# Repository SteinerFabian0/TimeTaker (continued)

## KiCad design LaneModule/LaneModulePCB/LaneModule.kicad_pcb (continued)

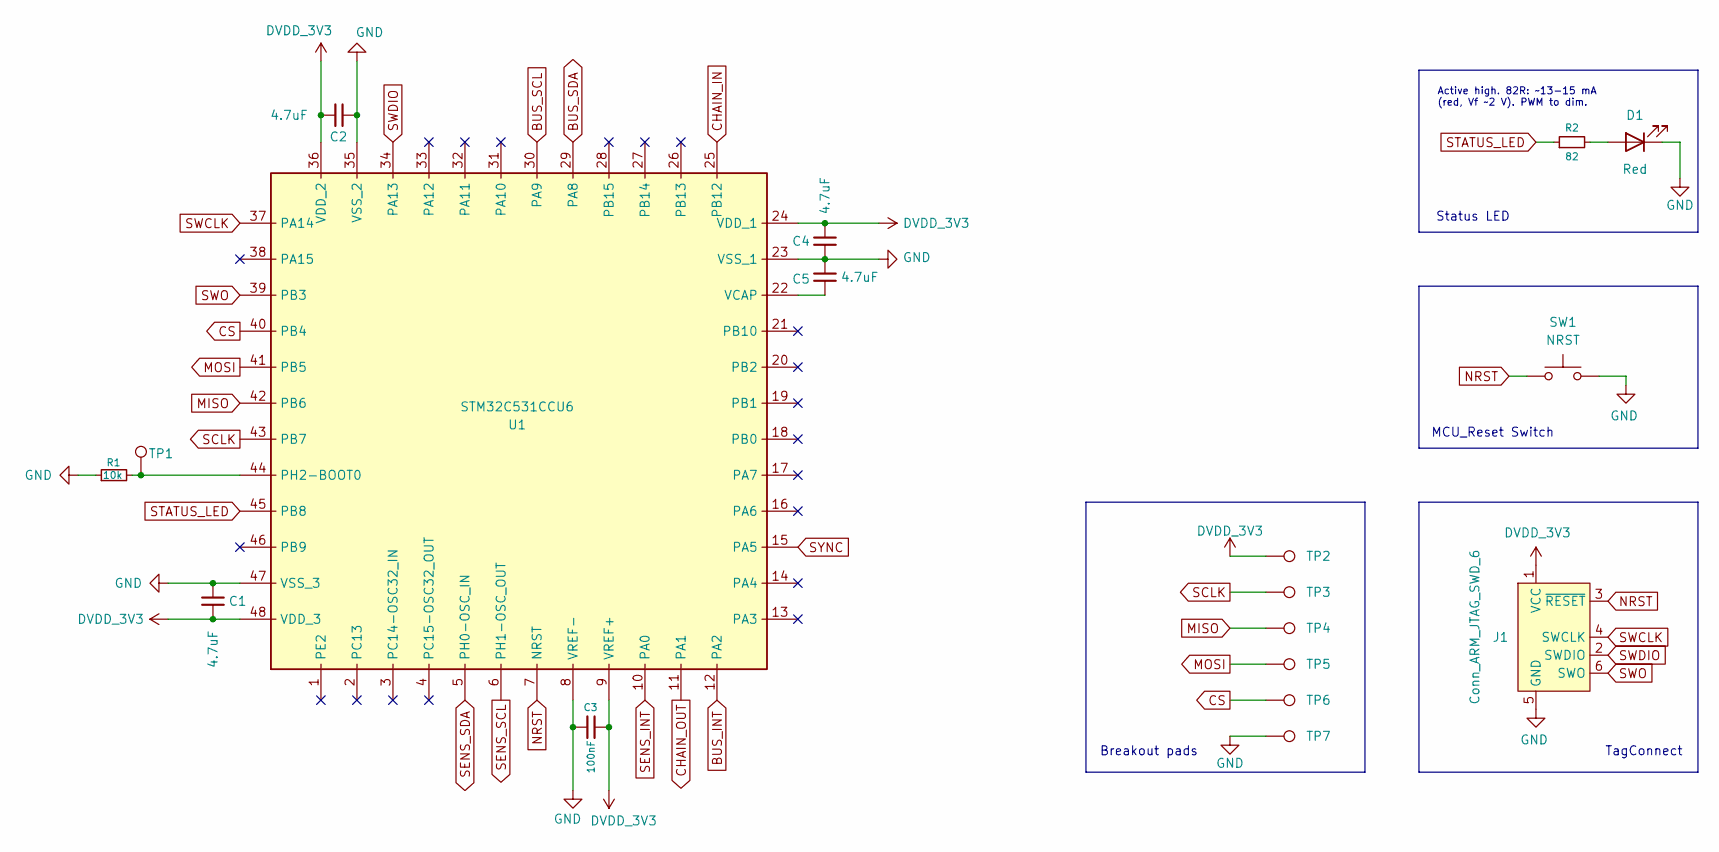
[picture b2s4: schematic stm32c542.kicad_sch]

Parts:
C1, C2, C4, C5: 4.7uF; C_0402_1005Metric; MPN CL05A475MP5NRNC; LCSC C23733
C3: 100nF; C_0402_1005Metric; MPN CL05B104KO5NNNC; LCSC C1525
D1: Red; LED_D5.0mm
J1: Conn_ARM_JTAG_SWD_6; Tag-Connect_TC2030-IDC-NL_2x03_P1.27mm_Vertical
R1: 10k; R_0603_1608Metric
R2: 82; R_0603_1608Metric
SW1: NRST; SW_SPST_TS-1088-xR025; MPN TS-1088-AR02016; LCSC C720477
TP1: TestPoint; Testpoint_1.2mm
TP2, TP3, TP4, TP5, TP6, TP7: TestPoint; TestPoint_Pad_1.5x1.5mm
U1: STM32C531CCU6; QFN50P700X700X60-49N-D; Manufacturer_Part_Number STM32C531CCU6

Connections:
BUS_INT: U1.12 (PA2); also elsewhere on the board
BUS_SCL: U1.30 (PA9); also elsewhere on the board
BUS_SDA: U1.29 (PA8); also elsewhere on the board
CHAIN_IN: U1.25 (PB12); also elsewhere on the board
CHAIN_OUT: U1.11 (PA1); also elsewhere on the board
CS: TP6.1 (1_1), U1.40 (PB4)
DVDD_3V3: C1.2, C2.2, C3.2, C4.1, J1.1 (VCC), TP2.1 (1_1), U1.9 (VREF+), U1.24 (VDD_1), U1.36 (VDD_2), U1.48 (VDD_3); also elsewhere on the board
GND: C1.1, C2.1, C3.1, C4.2, C5.1, D1.1 (K), J1.5 (GND), R1.1, SW1.2, TP7.1 (1_1), U1.8 (VREF-), U1.23 (VSS_1), U1.35 (VSS_2), U1.47 (VSS_3), U1.49 (VSS_4); also elsewhere on the board
MISO: TP4.1 (1_1), U1.42 (PB6)
MOSI: TP5.1 (1_1), U1.41 (PB5)
NRST: J1.3 (~RESET), SW1.1, U1.7 (NRST)
unnamed: D1.2 (A), R2.2
unnamed: R1.2, TP1.1 (1_1), U1.44 (PH2-BOOT0)
unnamed: C5.2, U1.22 (VCAP)
SCLK: TP3.1 (1_1), U1.43 (PB7)
SENS_INT: U1.10 (PA0); also elsewhere on the board
SENS_SCL: U1.6 (PH1-OSC_OUT); also elsewhere on the board
SENS_SDA: U1.5 (PH0-OSC_IN); also elsewhere on the board
STATUS_LED: R2.1, U1.45 (PB8)
SWCLK: J1.4 (SWCLK), U1.37 (PA14)
SWDIO: J1.2 (SWDIO), U1.34 (PA13)
SWO: J1.6 (SWO), U1.39 (PB3)
SYNC: U1.15 (PA5); also elsewhere on the board

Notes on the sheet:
MCU_Reset Switch
Breakout pads
TagConnect
Active high. 82R: ~13-15 mA (red, Vf ~2 V). PWM to dim.
Status LED

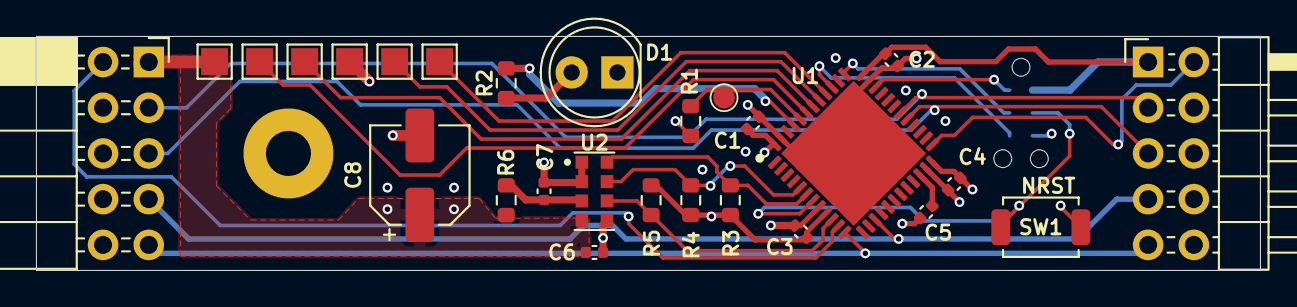
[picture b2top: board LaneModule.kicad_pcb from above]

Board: 4 copper layers, 68.0 x 13.0 mm, 29 parts (1 on the bottom side), 24 nets.

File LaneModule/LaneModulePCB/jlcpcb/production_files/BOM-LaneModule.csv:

Comment,Designator,Footprint,LCSC,Quantity
100nF,C3,C_0402_1005Metric,C1525,1
100uF,C8,CP_Elec_5x5.4,C72473,1
4.7uF,"C1,C2,C4,C5,C6,C7",C_0402_1005Metric,C23733,6
NRST,SW1,SW_SPST_TS-1088-xR025,C720477,1
VCNL4040M3OE,U2,VCNL4040M3OE,C142526,1
Red,D1,LED_D5.0mm,,1
Conn_02x05,J2,PinSocket_2x05_P2.54mm_Horizontal,,1
82,R2,R_0603_1608Metric,,1
10k,R5,R_0603_1608Metric,,1
STM32C531CCU6,U1,QFN50P700X700X60-49N-D,,1
22,R6,R_0603_1608Metric,,1
2.2k,R4,R_0603_1608Metric,,1
Conn_02x05,J3,PinHeader_2x05_P2.54mm_Horizontal,,1
10k,R1,R_0603_1608Metric,,1
2.2k,R3,R_0603_1608Metric,,1

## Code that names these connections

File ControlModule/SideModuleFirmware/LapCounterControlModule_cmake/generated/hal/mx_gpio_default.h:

/**
  ******************************************************************************
  * @file           : mx_gpio_default.h
  * @brief          : Header for mx_gpio_default.c file.
  ******************************************************************************
  * @attention
  *
  * Copyright (c) 2026 STMicroelectronics.
  * All rights reserved.
  *
  * This software is licensed under terms that can be found in the mx_stm32c5xx_hal_drivers_license.md file
  * in the same directory as the generated code.
  * If no mx_stm32c5xx_hal_drivers_license.md file comes with this software, it is provided AS-IS.
  *
  ******************************************************************************
  */

/* Define to prevent recursive inclusion -------------------------------------*/
#ifndef MX_GPIO_DEFAULT_H
#define MX_GPIO_DEFAULT_H

#ifdef __cplusplus
extern "C" {
#endif /* __cplusplus */

/* Includes ------------------------------------------------------------------*/
#include "stm32_hal.h"
#include "mx_def.h"

/* Exported types ------------------------------------------------------------*/
/* Exported constants --------------------------------------------------------*/
/******************************************************************************/
/* Exported defines for gpio_default in HAL layer                             */
/******************************************************************************/

/* Primary aliases for GPIO PA4 pin */
#define EXT_PWR_FAULT_PORT                              HAL_GPIOA
#define EXT_PWR_FAULT_PIN                               HAL_GPIO_PIN_4

/* Primary aliases for GPIO PA5 pin */
#define EXT_PWR_EN_PORT                                 HAL_GPIOA
#define EXT_PWR_EN_PIN                                  HAL_GPIO_PIN_5
#define EXT_PWR_EN_INIT_STATE                           HAL_GPIO_PIN_RESET
#define EXT_PWR_EN_ACTIVE_STATE                         HAL_GPIO_PIN_SET
#define EXT_PWR_EN_INACTIVE_STATE                       HAL_GPIO_PIN_RESET

/* Primary aliases for GPIO PA6 pin */
#define LANE_PWR_EN_PORT                                HAL_GPIOA
#define LANE_PWR_EN_PIN                                 HAL_GPIO_PIN_6
#define LANE_PWR_EN_INIT_STATE                          HAL_GPIO_PIN_RESET
#define LANE_PWR_EN_ACTIVE_STATE                        HAL_GPIO_PIN_SET
#define LANE_PWR_EN_INACTIVE_STATE                      HAL_GPIO_PIN_RESET

/* Primary aliases for GPIO PA10 pin */
#define CHAIN_OUT_PORT                                  HAL_GPIOA
#define CHAIN_OUT_PIN                                   HAL_GPIO_PIN_10
#define CHAIN_OUT_INIT_STATE                            HAL_GPIO_PIN_RESET
#define CHAIN_OUT_ACTIVE_STATE                          HAL_GPIO_PIN_SET
#define CHAIN_OUT_INACTIVE_STATE                        HAL_GPIO_PIN_RESET

/* Primary aliases for GPIO PA15(JTDI) pin */
#define BLE_GPIO2_PORT                                  HAL_GPIOA
#define BLE_GPIO2_PIN                                   HAL_GPIO_PIN_15

/* Primary aliases for GPIO PB0 pin */
#define SPI_CS2_PORT                                    HAL_GPIOB
#define SPI_CS2_PIN                                     HAL_GPIO_PIN_0
#define SPI_CS2_INIT_STATE                              HAL_GPIO_PIN_SET
#define SPI_CS2_ACTIVE_STATE                            HAL_GPIO_PIN_RESET
#define SPI_CS2_INACTIVE_STATE                          HAL_GPIO_PIN_SET

/* Primary aliases for GPIO PB1 pin */
#define SPI_CS1_PORT                                    HAL_GPIOB
#define SPI_CS1_PIN                                     HAL_GPIO_PIN_1
#define SPI_CS1_INIT_STATE                              HAL_GPIO_PIN_SET
#define SPI_CS1_ACTIVE_STATE                            HAL_GPIO_PIN_RESET
#define SPI_CS1_INACTIVE_STATE                          HAL_GPIO_PIN_SET

/* Primary aliases for GPIO PB4(NJTRST) pin */
#define BLE_GPIO1_PORT                                  HAL_GPIOB
#define BLE_GPIO1_PIN                                   HAL_GPIO_PIN_4

/* Primary aliases for GPIO PB5 pin */
#define BLE_IRQ_PORT                                    HAL_GPIOB
#define BLE_IRQ_PIN                                     HAL_GPIO_PIN_5

/* Primary aliases for GPIO PB12 pin */
#define USB_FAULT_PORT                                  HAL_GPIOB
#define USB_FAULT_PIN                                   HAL_GPIO_PIN_12

/* Primary aliases for GPIO PB14 pin */
#define BUS_INT_PORT                                    HAL_GPIOB
#define BUS_INT_PIN                                     HAL_GPIO_PIN_14

/* Primary aliases for GPIO PC13 pin */
#define BTN2_PORT                                       HAL_GPIOC
#define BTN2_PIN                                        HAL_GPIO_PIN_13

/* Primary aliases for GPIO PC15-OSC32_OUT(OSC32_OUT) pin */
#define BTN1_PORT                                       HAL_GPIOC
#define BTN1_PIN                                        HAL_GPIO_PIN_15

/* Primary aliases for GPIO PE2 pin */
#define BTN3_PORT                                       HAL_GPIOE
#define BTN3_PIN                                        HAL_GPIO_PIN_2

/* Exported macros -----------------------------------------------------------*/
/* Exported variables --------------------------------------------------------*/
/* Exported functions ------------------------------------------------------- */
/******************************************************************************/
/* Exported functions for gpio_default in HAL layer                           */
/******************************************************************************/
/**
  * @brief mx_gpio_default init function
  * This function configures the hardware resources used in this example
  * @retval 0  GPIO group correctly initialized
  * @retval -1 Issue detected during GPIO group initialization
  */
system_status_t mx_gpio_default_init(void);

/**
  * @brief  De-initialize gpio_default instance.
  */
system_status_t mx_gpio_default_deinit(void);

/**
  * @brief  Get the EXTI4 object.
  * @retval Pointer on the EXTI4 Handle
  */
hal_exti_handle_t *mx_gpio_default_exti4_gethandle(void);

/**
  * @brief  Get the EXTI5 object.
  * @retval Pointer on the EXTI5 Handle
  */
hal_exti_handle_t *mx_gpio_default_exti5_gethandle(void);

/**
  * @brief  Get the EXTI12 object.
  * @retval Pointer on the EXTI12 Handle
  */
hal_exti_handle_t *mx_gpio_default_exti12_gethandle(void);

/**
  * @brief  Get the EXTI14 object.
  * @retval Pointer on the EXTI14 Handle
  */
hal_exti_handle_t *mx_gpio_default_exti14_gethandle(void);

/**
  * @brief  Get the EXTI13 object.
  * @retval Pointer on the EXTI13 Handle
  */
hal_exti_handle_t *mx_gpio_default_exti13_gethandle(void);

/**
  * @brief  Get the EXTI15 object.
  * @retval Pointer on the EXTI15 Handle
  */
hal_exti_handle_t *mx_gpio_default_exti15_gethandle(void);

/**
  * @brief  Get the EXTI2 object.
  * @retval Pointer on the EXTI2 Handle
  */
hal_exti_handle_t *mx_gpio_default_exti2_gethandle(void);

/******************************************************************************/
/*                            EXTI Line4 interrupt                            */
/******************************************************************************/
void EXTI4_IRQHandler(void);

/******************************************************************************/
/*                           EXTI Line12 interrupt                            */
/******************************************************************************/
void EXTI12_IRQHandler(void);

/******************************************************************************/
/*                            EXTI Line5 interrupt                            */
/******************************************************************************/
void EXTI5_IRQHandler(void);

/******************************************************************************/
/*                           EXTI Line14 interrupt                            */
/******************************************************************************/
void EXTI14_IRQHandler(void);

/******************************************************************************/
/*                           EXTI Line13 interrupt                            */
/******************************************************************************/
void EXTI13_IRQHandler(void);

/******************************************************************************/
/*                           EXTI Line15 interrupt                            */
/******************************************************************************/
void EXTI15_IRQHandler(void);

/******************************************************************************/
/*                            EXTI Line2 interrupt                            */
/******************************************************************************/
void EXTI2_IRQHandler(void);

#ifdef __cplusplus
}
#endif /* __cplusplus */

#endif /* MX_GPIO_DEFAULT_H */

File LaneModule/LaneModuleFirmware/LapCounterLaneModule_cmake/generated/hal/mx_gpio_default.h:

/**
  ******************************************************************************
  * @file           : mx_gpio_default.h
  * @brief          : Header for mx_gpio_default.c file.
  ******************************************************************************
  * @attention
  *
  * Copyright (c) 2026 STMicroelectronics.
  * All rights reserved.
  *
  * This software is licensed under terms that can be found in the mx_stm32c5xx_hal_drivers_license.md file
  * in the same directory as the generated code.
  * If no mx_stm32c5xx_hal_drivers_license.md file comes with this software, it is provided AS-IS.
  *
  ******************************************************************************
  */

/* Define to prevent recursive inclusion -------------------------------------*/
#ifndef MX_GPIO_DEFAULT_H
#define MX_GPIO_DEFAULT_H

#ifdef __cplusplus
extern "C" {
#endif /* __cplusplus */

/* Includes ------------------------------------------------------------------*/
#include "stm32_hal.h"
#include "mx_def.h"

/* Exported types ------------------------------------------------------------*/
/* Exported constants --------------------------------------------------------*/
/******************************************************************************/
/* Exported defines for gpio_default in HAL layer                             */
/******************************************************************************/

/* Primary aliases for GPIO PA0 pin */
#define SENS_INT_PORT                                   HAL_GPIOA
#define SENS_INT_PIN                                    HAL_GPIO_PIN_0

/* Primary aliases for GPIO PA1 pin */
#define CHAIN_OUT_PORT                                  HAL_GPIOA
#define CHAIN_OUT_PIN                                   HAL_GPIO_PIN_1
#define CHAIN_OUT_INIT_STATE                            HAL_GPIO_PIN_RESET
#define CHAIN_OUT_ACTIVE_STATE                          HAL_GPIO_PIN_SET
#define CHAIN_OUT_INACTIVE_STATE                        HAL_GPIO_PIN_RESET

/* Primary aliases for GPIO PA2 pin */
#define BUS_INT_PORT                                    HAL_GPIOA
#define BUS_INT_PIN                                     HAL_GPIO_PIN_2
#define BUS_INT_INIT_STATE                              HAL_GPIO_PIN_SET
#define BUS_INT_ACTIVE_STATE                            HAL_GPIO_PIN_RESET
#define BUS_INT_INACTIVE_STATE                          HAL_GPIO_PIN_SET

/* Primary aliases for GPIO PB4(NJTRST) pin */
#define CS_PORT                                         HAL_GPIOB
#define CS_PIN                                          HAL_GPIO_PIN_4
#define CS_INIT_STATE                                   HAL_GPIO_PIN_SET
#define CS_ACTIVE_STATE                                 HAL_GPIO_PIN_RESET
#define CS_INACTIVE_STATE                               HAL_GPIO_PIN_SET

/* Primary aliases for GPIO PB12 pin */
#define CHAIN_IN_PORT                                   HAL_GPIOB
#define CHAIN_IN_PIN                                    HAL_GPIO_PIN_12

/* Exported macros -----------------------------------------------------------*/
/* Exported variables --------------------------------------------------------*/
/* Exported functions ------------------------------------------------------- */
/******************************************************************************/
/* Exported functions for gpio_default in HAL layer                           */
/******************************************************************************/
/**
  * @brief mx_gpio_default init function
  * This function configures the hardware resources used in this example
  * @retval 0  GPIO group correctly initialized
  * @retval -1 Issue detected during GPIO group initialization
  */
system_status_t mx_gpio_default_init(void);

/**
  * @brief  De-initialize gpio_default instance.
  */
system_status_t mx_gpio_default_deinit(void);

/**
  * @brief  Get the EXTI0 object.
  * @retval Pointer on the EXTI0 Handle
  */
hal_exti_handle_t *mx_gpio_default_exti0_gethandle(void);

/**
  * @brief  Get the EXTI12 object.
  * @retval Pointer on the EXTI12 Handle
  */
hal_exti_handle_t *mx_gpio_default_exti12_gethandle(void);

/******************************************************************************/
/*                            EXTI Line0 interrupt                            */
/******************************************************************************/
void EXTI0_IRQHandler(void);

/******************************************************************************/
/*                           EXTI Line12 interrupt                            */
/******************************************************************************/
void EXTI12_IRQHandler(void);

#ifdef __cplusplus
}
#endif /* __cplusplus */

#endif /* MX_GPIO_DEFAULT_H */

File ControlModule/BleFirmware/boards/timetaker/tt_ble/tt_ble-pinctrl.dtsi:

/*
 * TimeTaker BLE bridge pin control.
 *
 * The UART net names are the STM's view: UART1_TX (STM PB6) is the nRF's RX,
 * UART1_RX (STM PB7) is the nRF's TX. BLE_FIRMWARE_GUIDE.md §3.2.
 */

&pinctrl {
	uart0_default: uart0_default {
		group1 {
			psels = <NRF_PSEL(UART_TX, 0, 18)>;
		};
		group2 {
			psels = <NRF_PSEL(UART_RX, 0, 16)>;
			/* Keeps the line idle while the STM is in reset. */
			bias-pull-up;
		};
	};

	uart0_sleep: uart0_sleep {
		group1 {
			psels = <NRF_PSEL(UART_TX, 0, 18)>,
				<NRF_PSEL(UART_RX, 0, 16)>;
			low-power-enable;
		};
	};
};
